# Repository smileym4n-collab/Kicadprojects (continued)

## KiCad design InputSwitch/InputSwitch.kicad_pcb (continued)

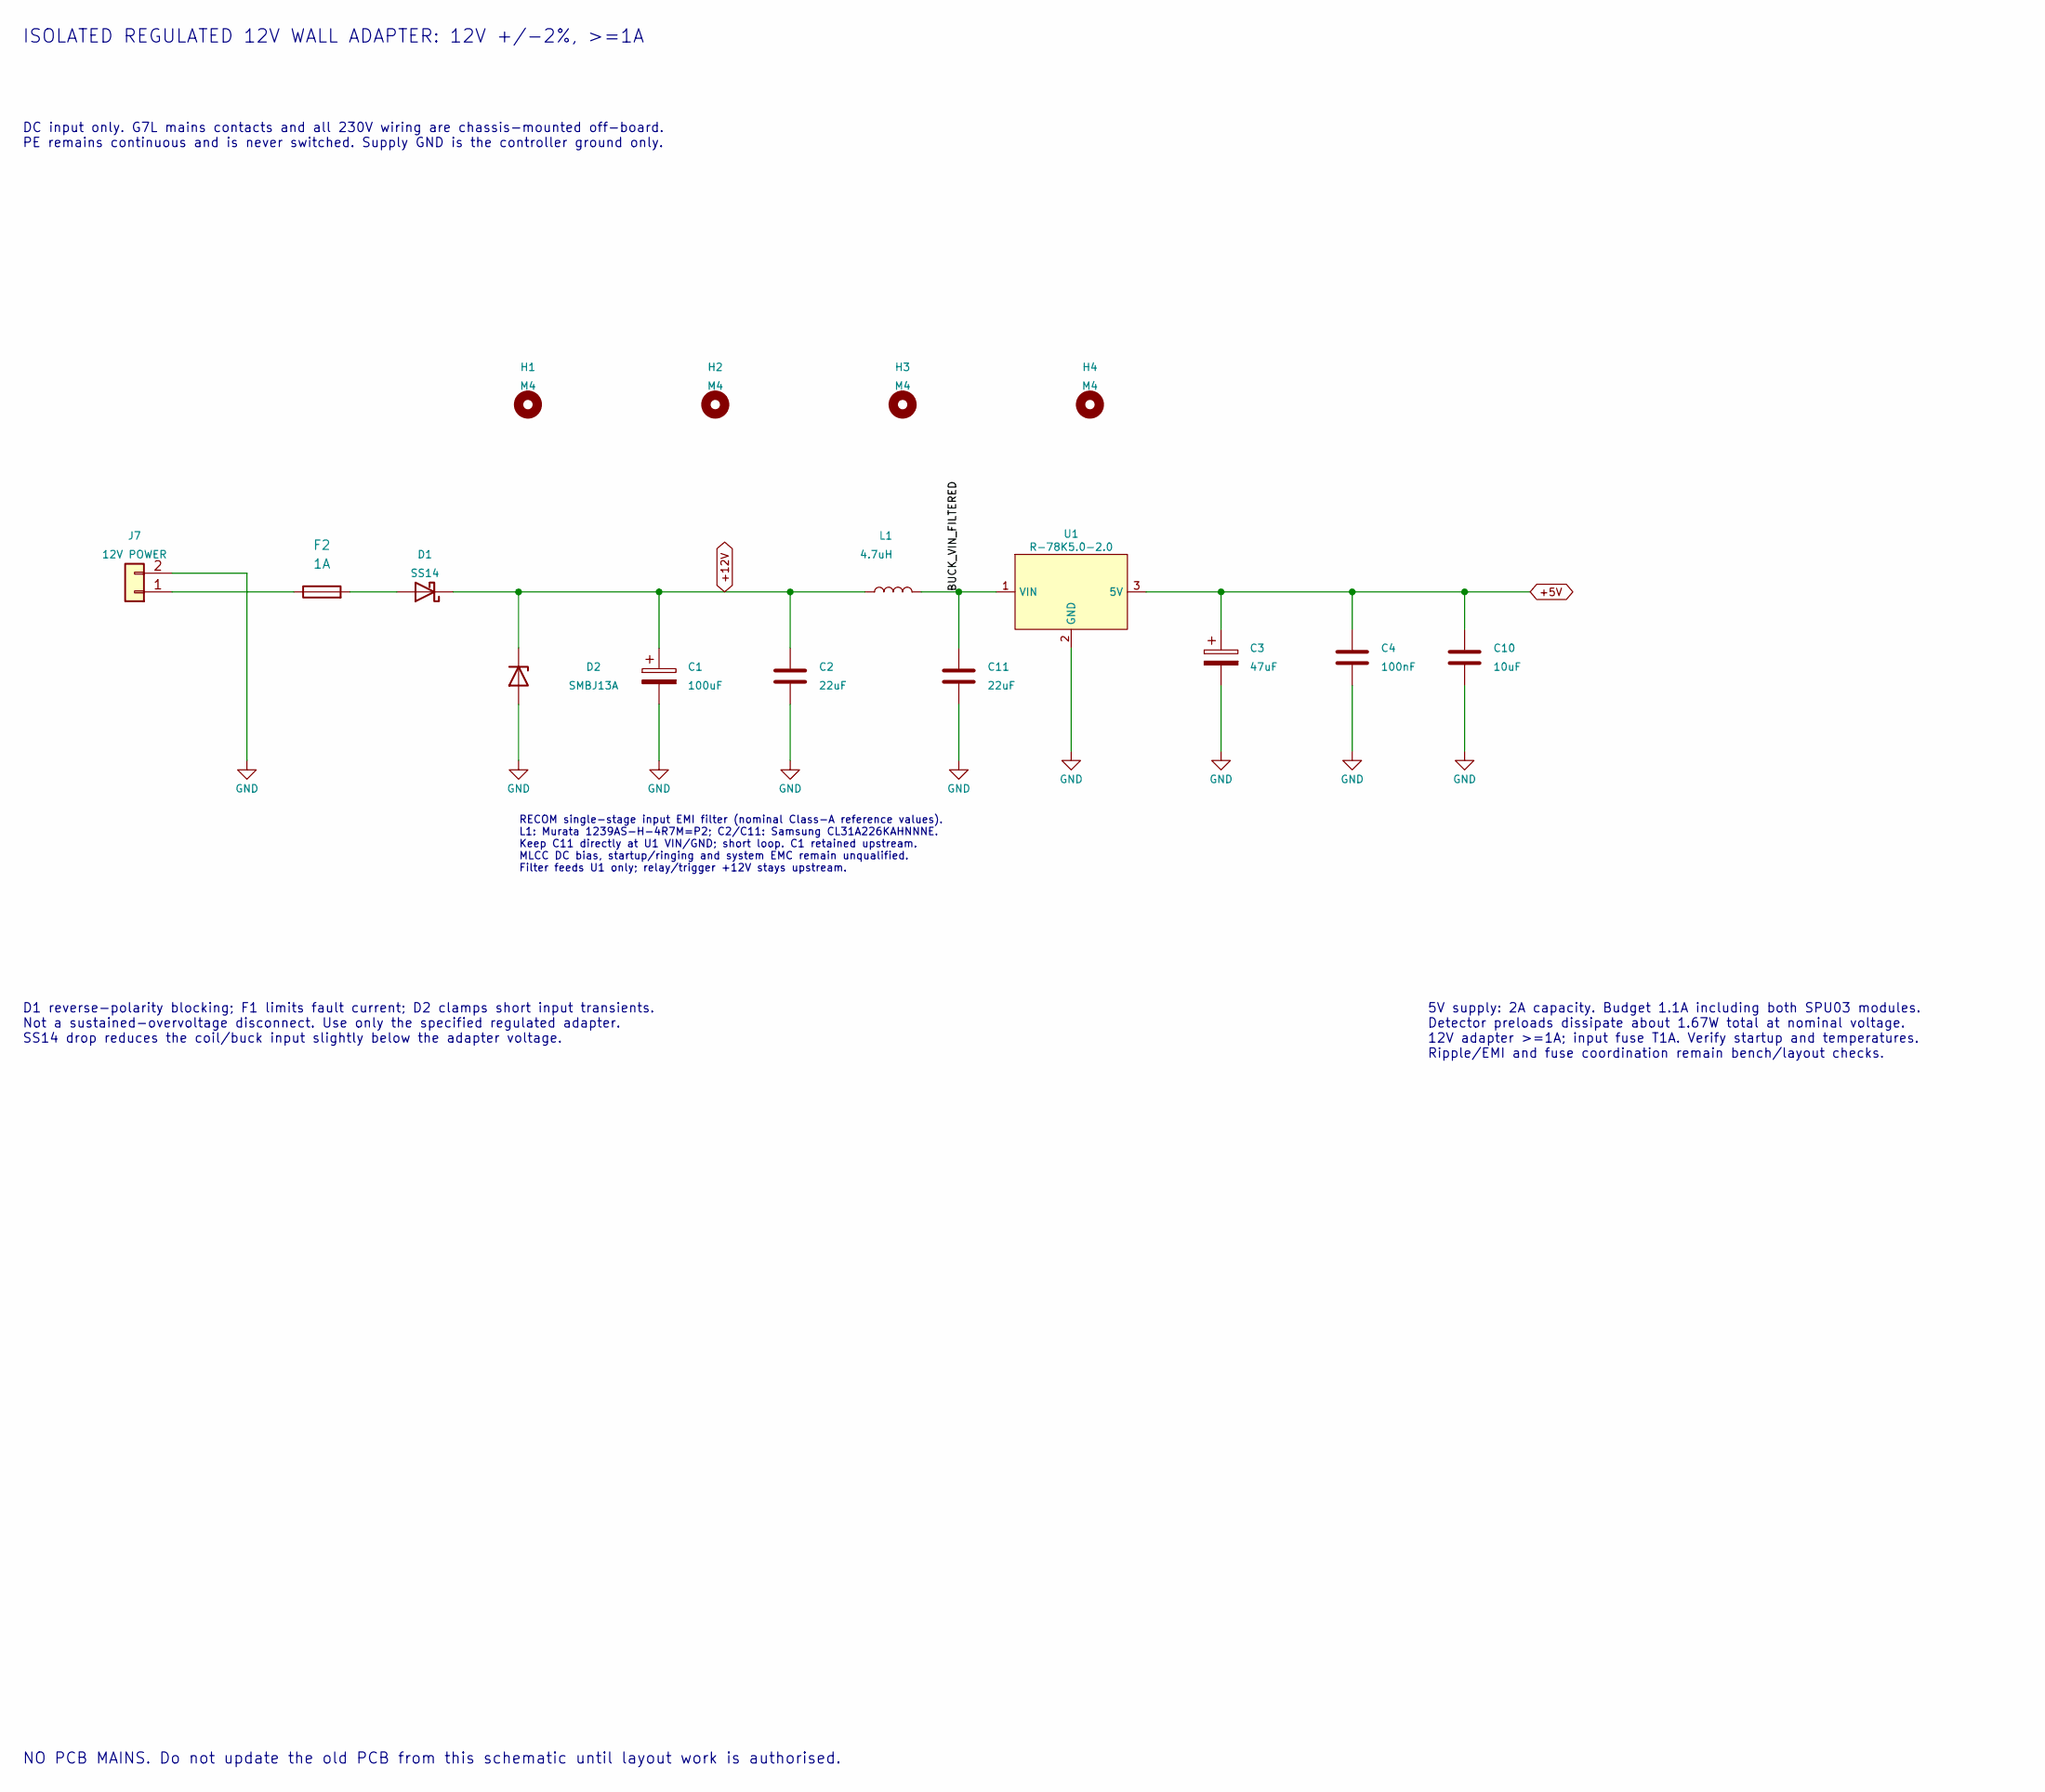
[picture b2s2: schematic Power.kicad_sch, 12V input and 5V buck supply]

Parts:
C1: 100uF; CP_Radial_D6.3mm_P2.50mm; Manufacturer_Part_Number EEUFR1C101
C2, C11: 22uF; C_1206_3216Metric_Pad1.33x1.80mm_HandSolder; MPN CL31A226KAHNNNE
C3: 47uF; CP_Radial_D5.0mm_P2.50mm; Manufacturer_Part_Number EEUFR1E470H
C4: 100nF; C_1206_3216Metric_Pad1.33x1.80mm_HandSolder; Manufacturer_Part_Number C1206C104K5RACTU
C10: 10uF; C_1206_3216Metric_Pad1.33x1.80mm_HandSolder; Manufacturer_Part_Number TMK316B7106KL-TD
D1: SS14; D_SMA; Manufacturer_Part_Number SS14+
D2: SMBJ13A; D_SMB; Manufacturer_Part_Number SMBJ13A
F2: 1A; Fuseholder_Cylinder-5x20mm_Schurter_0031_8201_Horizontal_Op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
H1, H2, H3, H4: M4; MountingHole_4.3mm_M4
J7: 12V POWER; JST_XH_B2B-XH-A_1x02_P2.50mm_Vertical; Manufacturer_Part_Number MC34629
L1: 4.7uH; L_1008_2520Metric; MPN 1239AS-H-4R7M=P2
U1: R-78K5.0-2.0; R78B_2A_SIP3; Manufacturer_Part_Number R-78K5.0-2.0

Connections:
+5V: C3.1, C4.1, C10.1, U1.3 (5V); also elsewhere on the board
+12V: C1.1, C2.1, D1.1 (K), D2.1 (K), L1.1; also elsewhere on the board
/12V input and 5V buck supply/BUCK_VIN_FILTERED: C11.1, L1.2, U1.1 (VIN)
GND: C1.2, C2.2, C3.2, C4.2, C10.2, C11.2, D2.2 (A), J7.2, U1.2 (GND); also elsewhere on the board
unnamed: D1.2 (A), F2.2
unnamed: F2.1, J7.1

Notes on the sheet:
D1 reverse-polarity blocking; F1 limits fault current; D2 clamps short input transients. Not a sustained-overvoltage disconnect. Use only the specified regulated adapter. SS14 drop reduces the coil/buck input slightly below the adapter voltage.
RECOM single-stage input EMI filter (nominal Class-A reference values). L1: Murata 1239AS-H-4R7M=P2; C2/C11: Samsung CL31A226KAHNNNE. Keep C11 directly at U1 VIN/GND; short loop. C1 retained upstream. MLCC DC bias, startup/ringing and system EMC remain unqualified. Filter feeds U1 only; relay/trigg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
NO PCB MAINS. Do not update the old PCB from this schematic until layout work is authorised.
5V supply: 2A capacity. Budget 1.1A including both SPU03 modules. Detector preloads dissipate about 1.67W total at nominal voltage. 12V adapter >=1A; input fuse T1A. Verify startup and temperatures. Ripple/EMI and fuse coordination remain bench/layout checks.
DC input only. G7L mains contacts and all 230V wiring are chassis-mounted off-board. PE remains continuous and is never switched. Supply GND is the controller ground only.
ISOLATED REGULATED 12V WALL ADAPTER: 12V +/-2%, >=1A

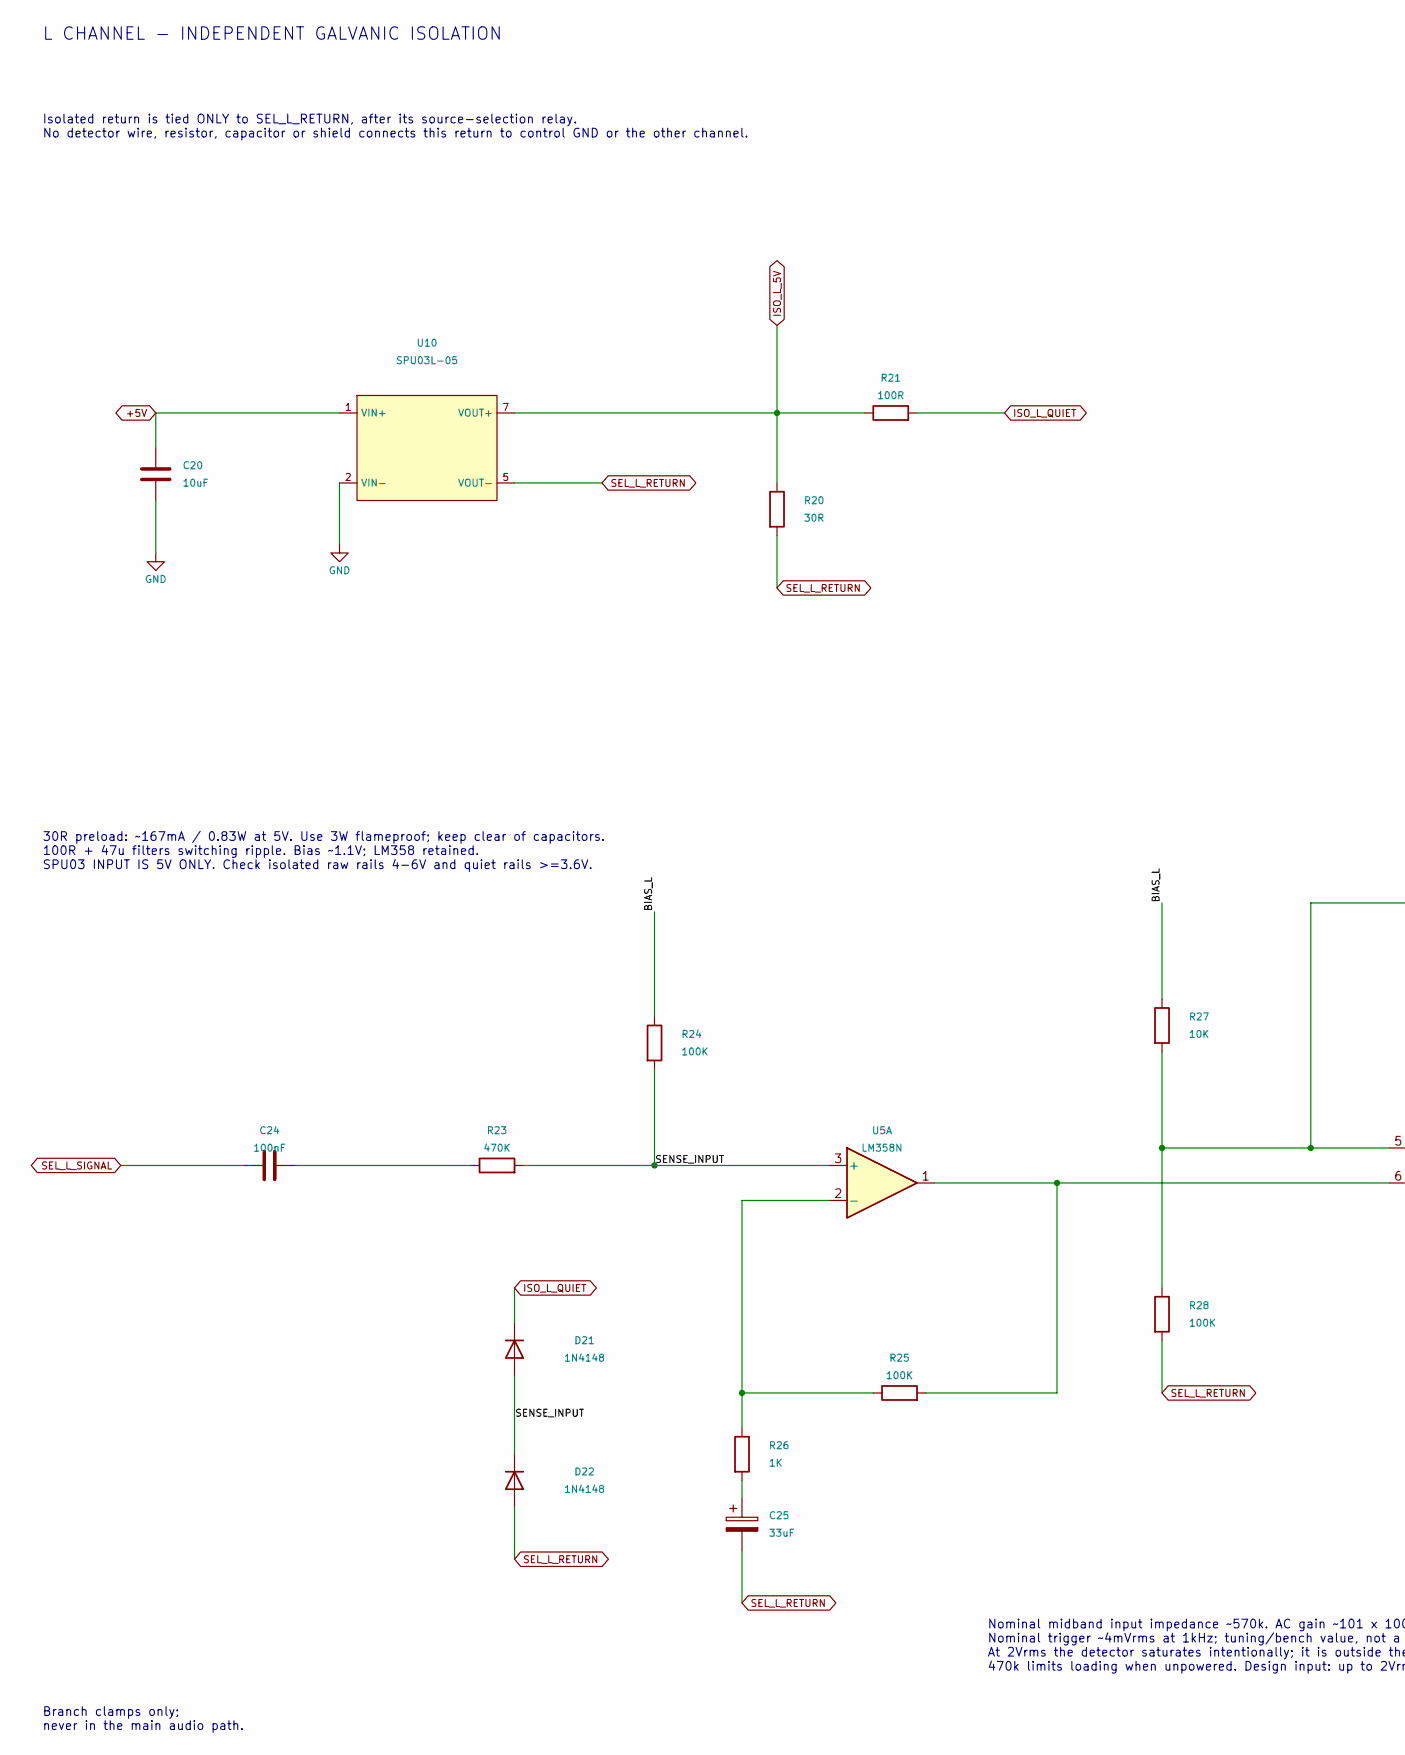
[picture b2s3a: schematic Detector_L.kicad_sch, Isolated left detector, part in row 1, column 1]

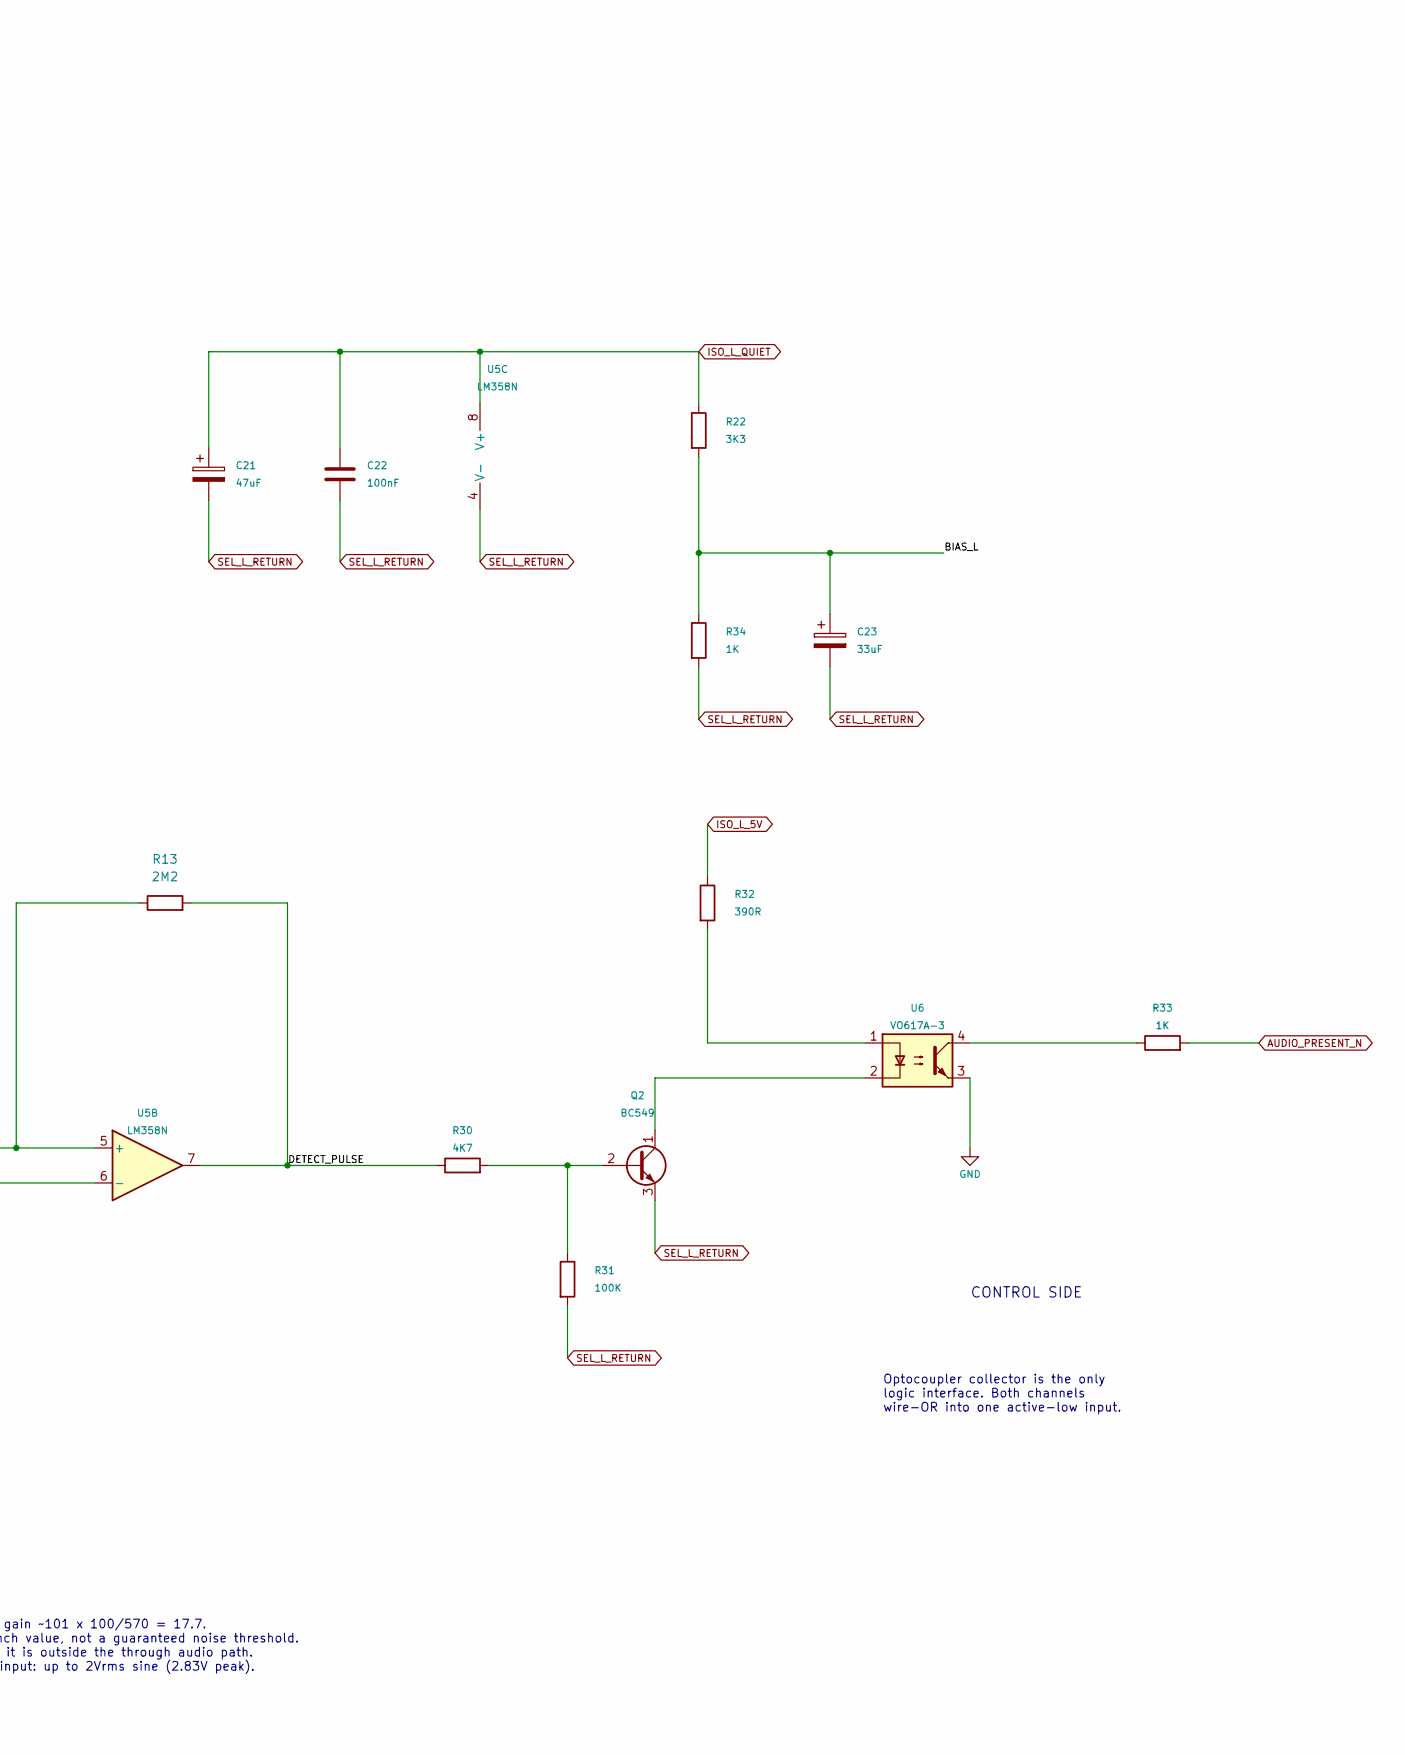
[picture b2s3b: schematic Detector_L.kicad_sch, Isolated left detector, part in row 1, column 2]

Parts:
C20: 10uF; C_1206_3216Metric_Pad1.33x1.80mm_HandSolder
C21: 47uF; CP_Radial_D5.0mm_P2.50mm
C22: 100nF; C_1206_3216Metric_Pad1.33x1.80mm_HandSolder
C23, C25: 33uF; CP_Radial_D5.0mm_P2.50mm
C24: 100nF; C_Rect_L7.0mm_W2.5mm_P5.00mm
D21, D22: 1N4148; D_DO-35_SOD27_P7.62mm_Horizontal
Q2: BC549; TO-92_Wide
R13: 2M2; R_0805_2012Metric_Pad1.20x1.40mm_HandSolder
R20: 30R; R_Axial_DIN0617_L17.0mm_D6.0mm_P25.40mm_Horizontal
R21: 100R; R_0805_2012Metric_Pad1.20x1.40mm_HandSolder
R22: 3K3; R_0805_2012Metric_Pad1.20x1.40mm_HandSolder
R23: 470K; R_0805_2012Metric_Pad1.20x1.40mm_HandSolder
R24, R25, R28, R31: 100K; R_0805_2012Metric_Pad1.20x1.40mm_HandSolder
R26, R33, R34: 1K; R_0805_2012Metric_Pad1.20x1.40mm_HandSolder
R27: 10K; R_0805_2012Metric_Pad1.20x1.40mm_HandSolder
R30: 4K7; R_0805_2012Metric_Pad1.20x1.40mm_HandSolder
R32: 390R; R_0805_2012Metric_Pad1.20x1.40mm_HandSolder
U5: LM358N; DIP-8_W7.62mm_Socket
U6: VO617A-3; DIP-4_W7.62mm
U10: SPU03L-05; SPU03L_05_SIP7

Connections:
+5V: C20.1, U10.1 (VIN+); also elsewhere on the board
/Isolated left detector/BIAS_L: C23.1, R22.2, R24.1, R27.1, R34.1
/Isolated left detector/DETECT_PULSE: R13.2, R30.1, U5.7
/Isolated left detector/SENSE_INPUT: D21.2 (A), D22.1 (K), R23.2, R24.2, U5.3 (+)
AUDIO_PRESENT_N: R33.2; also elsewhere on the board
GND: C20.2, U6.3, U10.2 (VIN-); also elsewhere on the board
ISO_L_5V: R20.1, R21.1, R32.1, U10.7 (VOUT+)
ISO_L_QUIET: C21.1, C22.1, D21.1 (K), R21.2, R22.1, U5.8 (V+)
unnamed: C24.2, R23.1
unnamed: C25.1, R26.2
unnamed: Q2.2 (B), R30.2, R31.1
unnamed: Q2.1 (C), U6.2
unnamed: R32.2, U6.1
unnamed: R33.1, U6.4
unnamed: R25.1, R26.1, U5.2 (-)
unnamed: R13.1, R27.2, R28.1, U5.5 (+)
unnamed: R25.2, U5.1, U5.6 (-)
SEL_L_RETURN: C21.2, C22.2, C23.2, C25.2, D22.2 (A), Q2.3 (E), R20.2, R28.2, R31.2, R34.2, U5.4 (V-), U10.5 (VOUT-); also elsewhere on the board
SEL_L_SIGNAL: C24.1; also elsewhere on the board

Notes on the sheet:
L CHANNEL - INDEPENDENT GALVANIC ISOLATION
Nominal midband input impedance ~570k. AC gain ~101 x 100/570 = 17.7. Nominal trigger ~4mVrms at 1kHz; tuning/bench value, not a guaranteed noise threshold. At 2Vrms the detector saturates intentionally; it is outside the through audio path. 470k limits loading when unpowered. Design input: up to 2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
Isolated return is tied ONLY to SEL_L_RETURN, after its source-selection relay. No detector wire, resistor, capacitor or shield connects this return to control GND or the other channel.
CONTROL SIDE
Branch clamps only; never in the main audio path.
30R preload: ~167mA / 0.83W at 5V. Use 3W flameproof; keep clear of capacitors. 100R + 47u filters switching ripple. Bias ~1.1V; LM358 retained. SPU03 INPUT IS 5V ONLY. Check isolated raw rails 4-6V and quiet rails >=3.6V.
Optocoupler collector is the only logic interface. Both channels wire-OR into one active-low input.

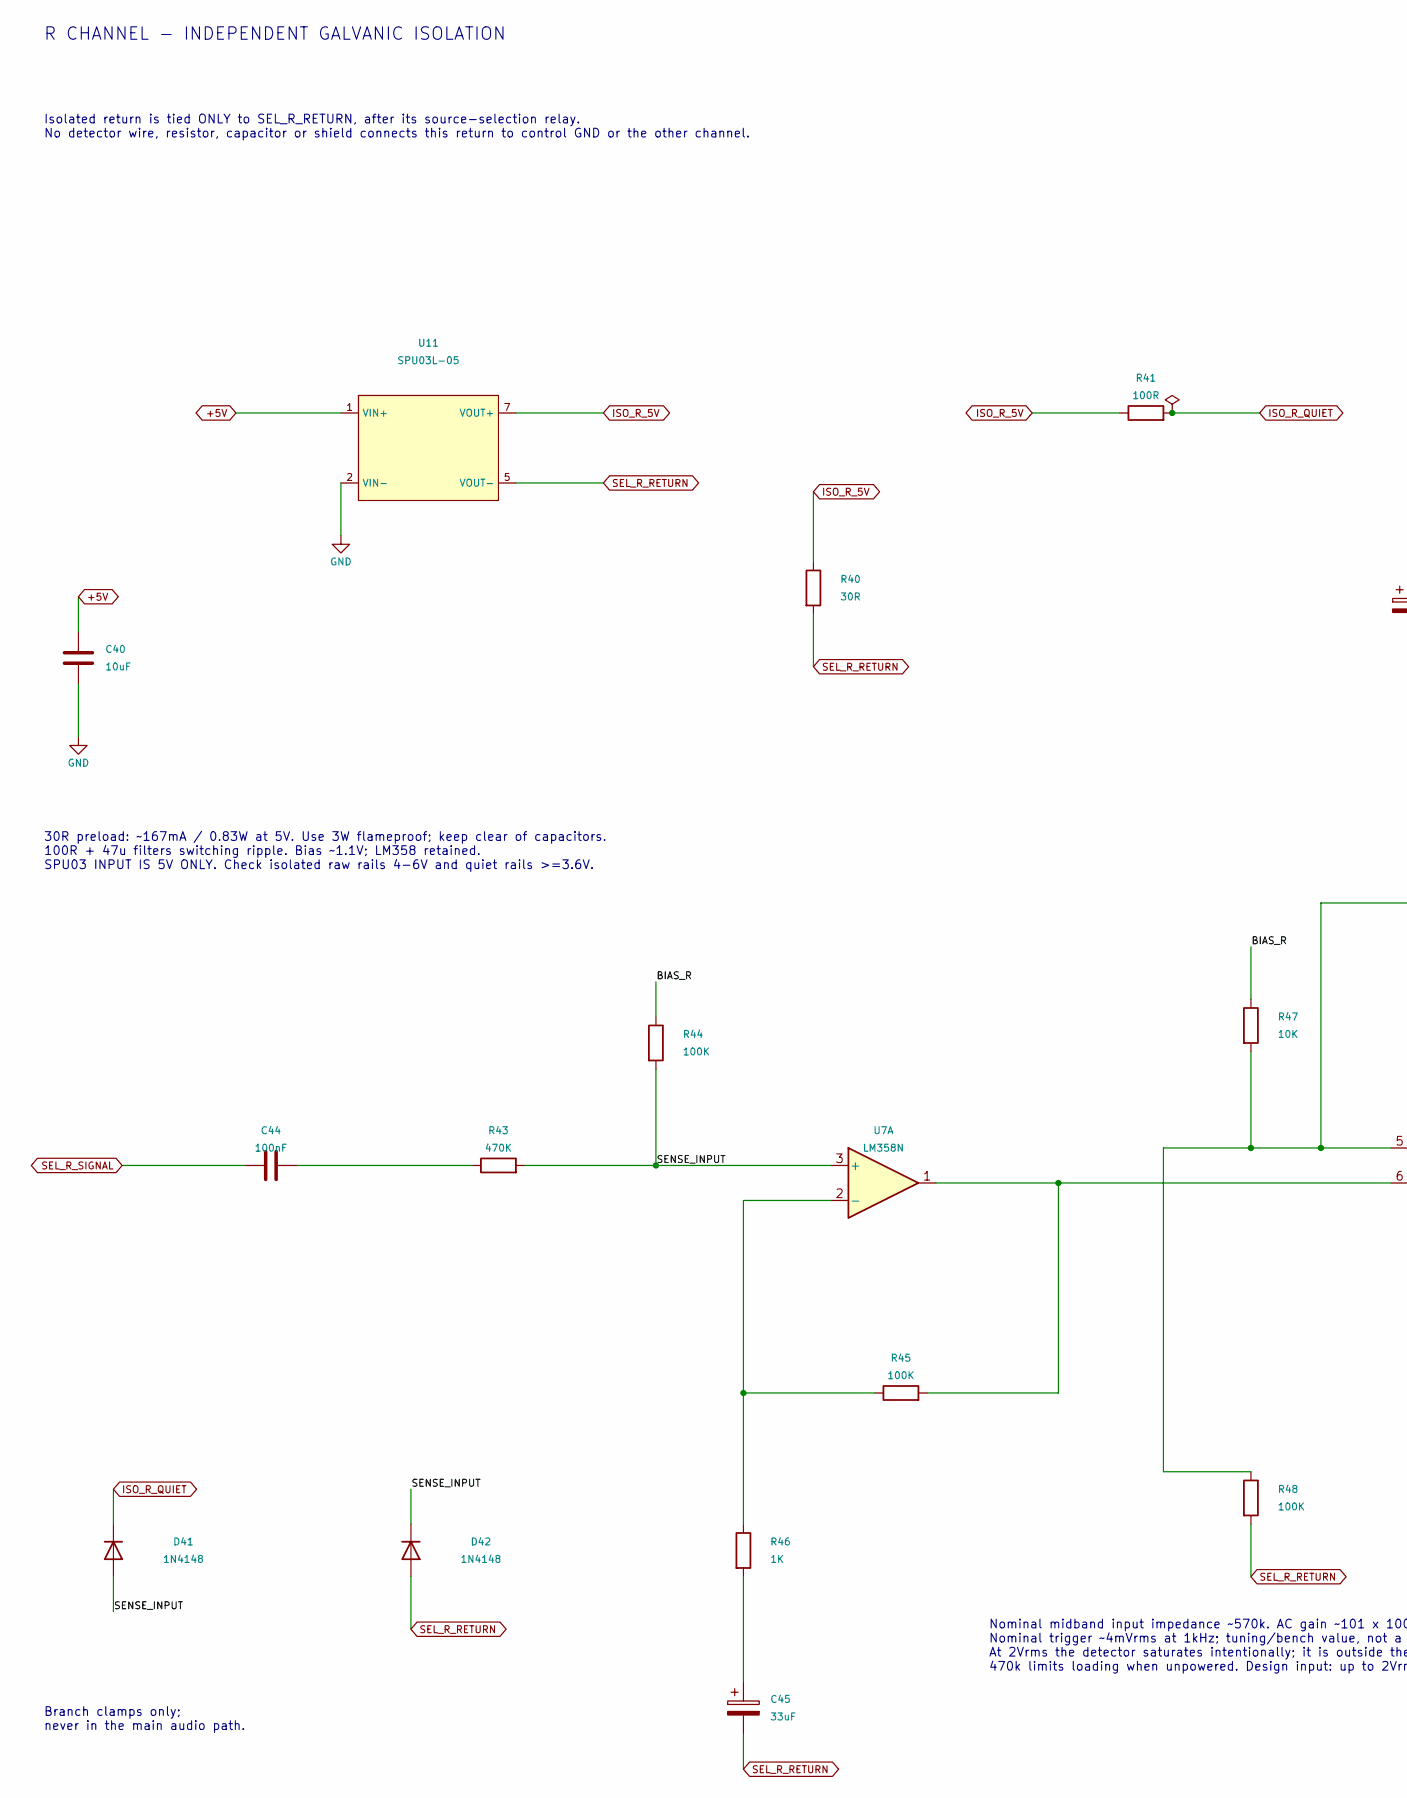
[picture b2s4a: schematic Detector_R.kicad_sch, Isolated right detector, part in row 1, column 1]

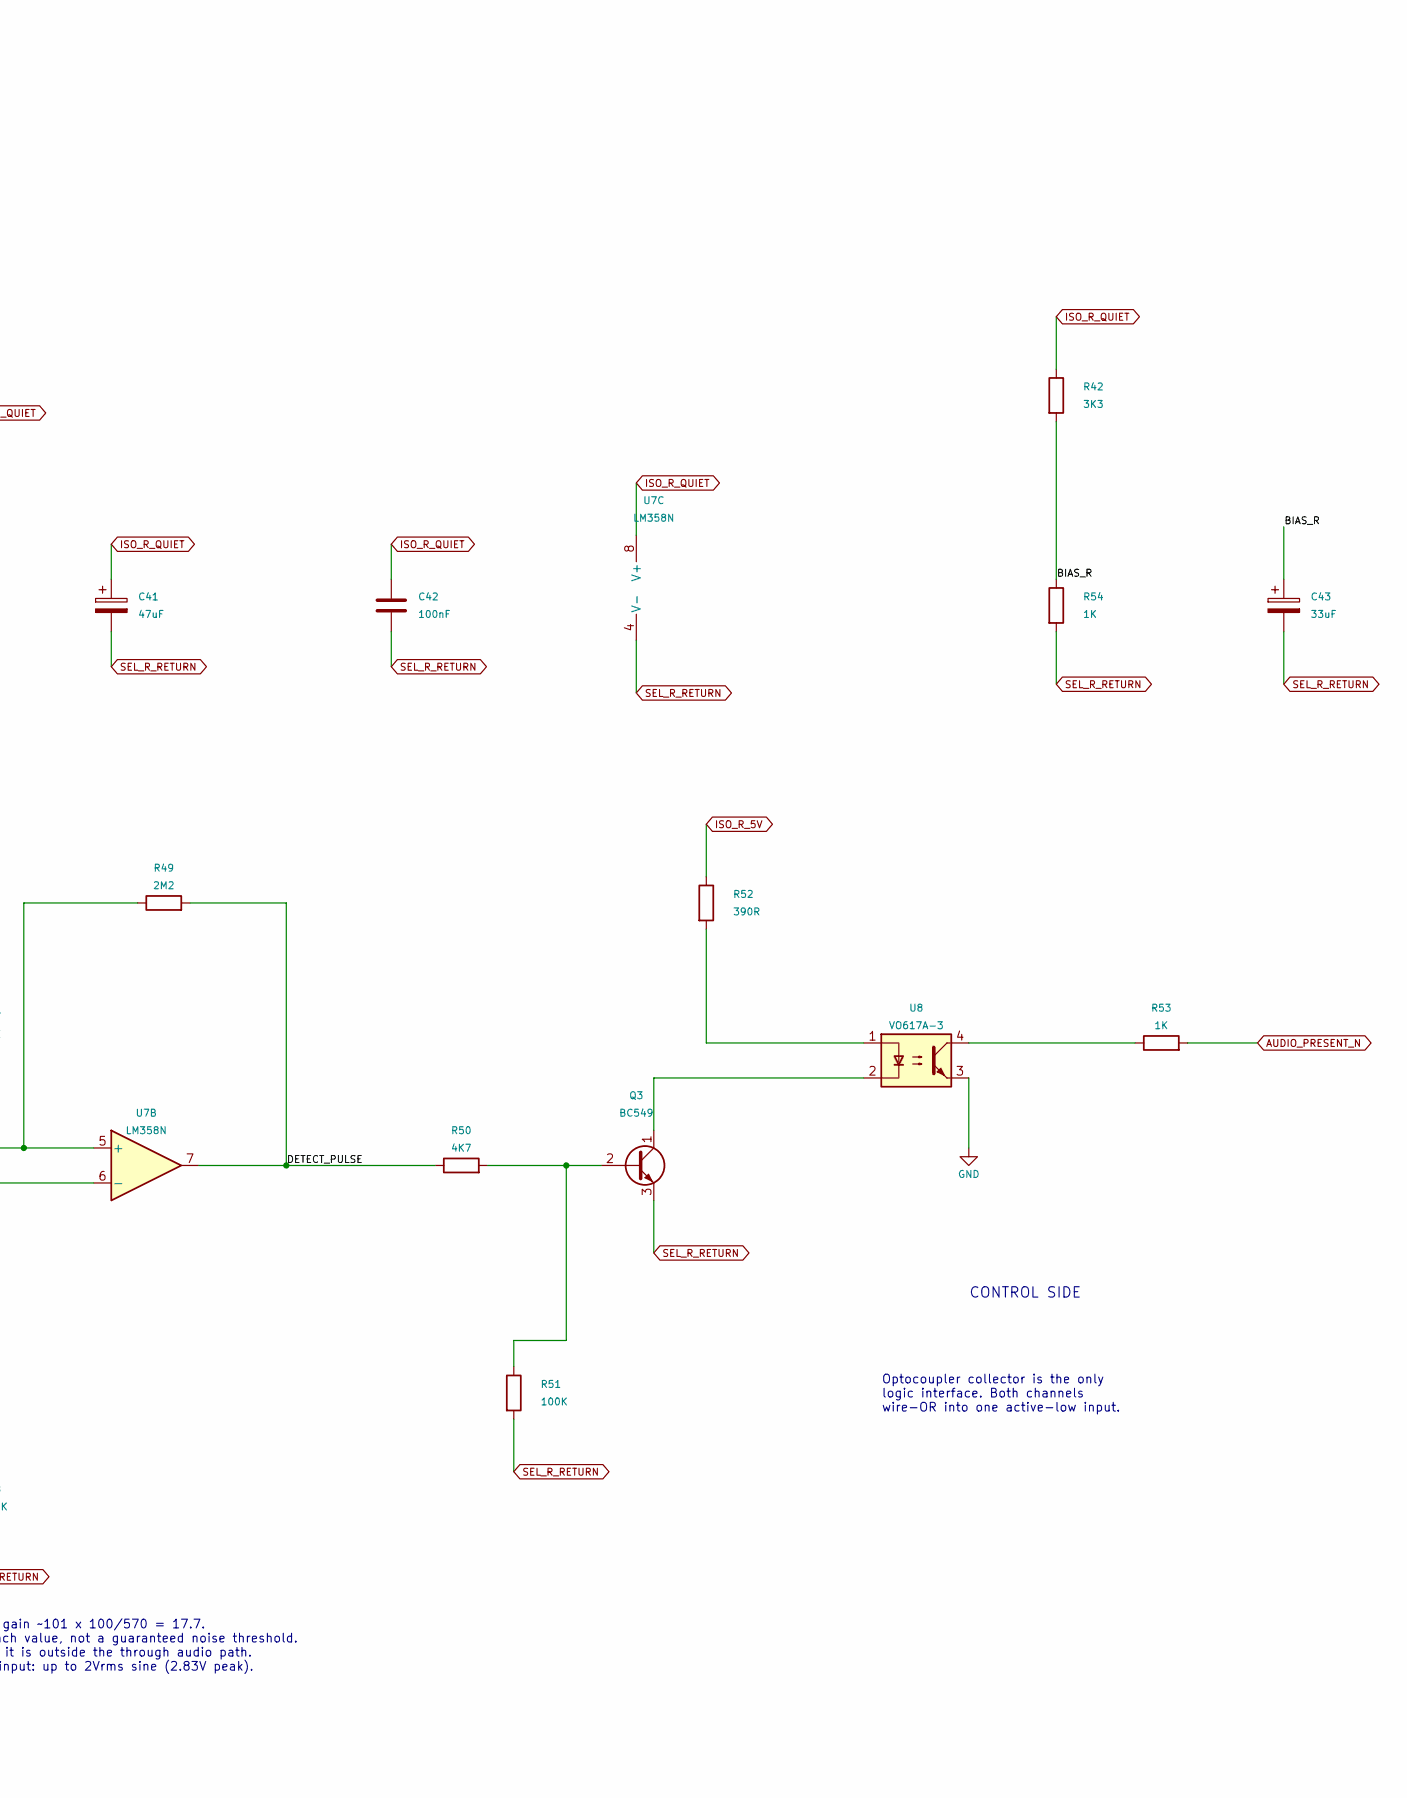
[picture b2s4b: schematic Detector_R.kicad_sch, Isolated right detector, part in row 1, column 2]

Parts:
C40: 10uF; C_1206_3216Metric_Pad1.33x1.80mm_HandSolder; Manufacturer_Part_Number TMK316B7106KL-TD
C41: 47uF; CP_Radial_D5.0mm_P2.50mm; Manufacturer_Part_Number EEUFR1E470H
C42: 100nF; C_1206_3216Metric_Pad1.33x1.80mm_HandSolder; Manufacturer_Part_Number C1206C104K5RACTU
C43, C45: 33uF; CP_Radial_D5.0mm_P2.50mm; Manufacturer_Part_Number MCKSK050M330D11S
C44: 100nF; C_Rect_L7.0mm_W2.5mm_P5.00mm; Manufacturer_Part_Number R82DC3100DQ50J
D41, D42: 1N4148; D_DO-35_SOD27_P7.62mm_Horizontal; Manufacturer_Part_Number 1N4148
Q3: BC549; TO-92_Wide; Manufacturer_Part_Number BC549
R40: 30R; R_Axial_DIN0617_L17.0mm_D6.0mm_P25.40mm_Horizontal; Manufacturer_Part_Number MCKNP03WJ0330AA9
R41: 100R; R_0805_2012Metric_Pad1.20x1.40mm_HandSolder; Manufacturer_Part_Number 100RThickFilm
R42: 3K3; R_0805_2012Metric_Pad1.20x1.40mm_HandSolder; Manufacturer_Part_Number RMCF0805FT3K30
R43: 470K; R_0805_2012Metric_Pad1.20x1.40mm_HandSolder; Manufacturer_Part_Number RT0805FRE07470KL
R44, R45, R48, R51: 100K; R_0805_2012Metric_Pad1.20x1.40mm_HandSolder; Manufacturer_Part_Number 100KThickFilm
R46, R53, R54: 1K; R_0805_2012Metric_Pad1.20x1.40mm_HandSolder; Manufacturer_Part_Number 1KThickFilm
R47: 10K; R_0805_2012Metric_Pad1.20x1.40mm_HandSolder; Manufacturer_Part_Number 660-RK73B2ATTD103J
R49: 2M2; R_0805_2012Metric_Pad1.20x1.40mm_HandSolder; Manufacturer_Part_Number RC0805FR-072M2L
R50: 4K7; R_0805_2012Metric_Pad1.20x1.40mm_HandSolder; Manufacturer_Part_Number RMCF0805FT4K70
R52: 390R; R_0805_2012Metric_Pad1.20x1.40mm_HandSolder; Manufacturer_Part_Number RMCF0805FT390R
U7: LM358N; DIP-8_W7.62mm_Socket; Manufacturer_Part_Number LM358
U8: VO617A-3; DIP-4_W7.62mm; Manufacturer_Part_Number VO617A-3
U11: SPU03L-05; SPU03L_05_SIP7; Manufacturer_Part_Number SPU03L-05

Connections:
+5V: C40.1, U11.1 (VIN+); also elsewhere on the board
/Isolated right detector/BIAS_R: C43.1, R42.2, R44.1, R47.1, R54.1
/Isolated right detector/DETECT_PULSE: R49.2, R50.1, U7.7
/Isolated right detector/SENSE_INPUT: D41.2 (A), D42.1 (K), R43.2, R44.2, U7.3 (+)
AUDIO_PRESENT_N: R53.2; also elsewhere on the board
GND: C40.2, U8.3, U11.2 (VIN-); also elsewhere on the board
ISO_R_5V: R40.1, R41.1, R52.1, U11.7 (VOUT+)
ISO_R_QUIET: C41.1, C42.1, D41.1 (K), R41.2, R42.1, U7.8 (V+)
unnamed: C44.2, R43.1
unnamed: C45.1, R46.2
unnamed: Q3.2 (B), R50.2, R51.1
unnamed: Q3.1 (C), U8.2
unnamed: R52.2, U8.1
unnamed: R53.1, U8.4
unnamed: R45.1, R46.1, U7.2 (-)
unnamed: R47.2, R48.1, R49.1, U7.5 (+)
unnamed: R45.2, U7.1, U7.6 (-)
SEL_R_RETURN: C41.2, C42.2, C43.2, C45.2, D42.2 (A), Q3.3 (E), R40.2, R48.2, R51.2, R54.2, U7.4 (V-), U11.5 (VOUT-); also elsewhere on the board
SEL_R_SIGNAL: C44.1; also elsewhere on the board

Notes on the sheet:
Nominal midband input impedance ~570k. AC gain ~101 x 100/570 = 17.7. Nominal trigger ~4mVrms at 1kHz; tuning/bench value, not a guaranteed noise threshold. At 2Vrms the detector saturates intentionally; it is outside the through audio path. 470k limits loading when unpowered. Design input: up to 2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
30R preload: ~167mA / 0.83W at 5V. Use 3W flameproof; keep clear of capacitors. 100R + 47u filters switching ripple. Bias ~1.1V; LM358 retained. SPU03 INPUT IS 5V ONLY. Check isolated raw rails 4-6V and quiet rails >=3.6V.
CONTROL SIDE
Branch clamps only; never in the main audio path.
Optocoupler collector is the only logic interface. Both channels wire-OR into one active-low input.
R CHANNEL - INDEPENDENT GALVANIC ISOLATION
Isolated return is tied ONLY to SEL_R_RETURN, after its source-selection relay. No detector wire, resistor, capacitor or shield connects this return to control GND or the other channel.
